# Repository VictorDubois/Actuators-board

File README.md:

Compact ESP32-based PCB, to control:
- 2 steppers
- 8 hobby servomotors (dedicated 6V DC-DC)
- AX12 Dynamixel numeric servomotors
- Addressable LEDs
- 2 vaccum sensors
- 4 generic GPIO connectors
- 3 generic I2C connectors
- 2 Krabi-Bus (12V/12V power/24V power/CAN)

[The code is available here](https://github.com/VictorDubois/ActuatorBoardCode)

[Click for online viewer

](https://kicanvas.org/?repo=https%3A%2F%2Fgithub.com%2FVictorDubois%2FActuators-board)

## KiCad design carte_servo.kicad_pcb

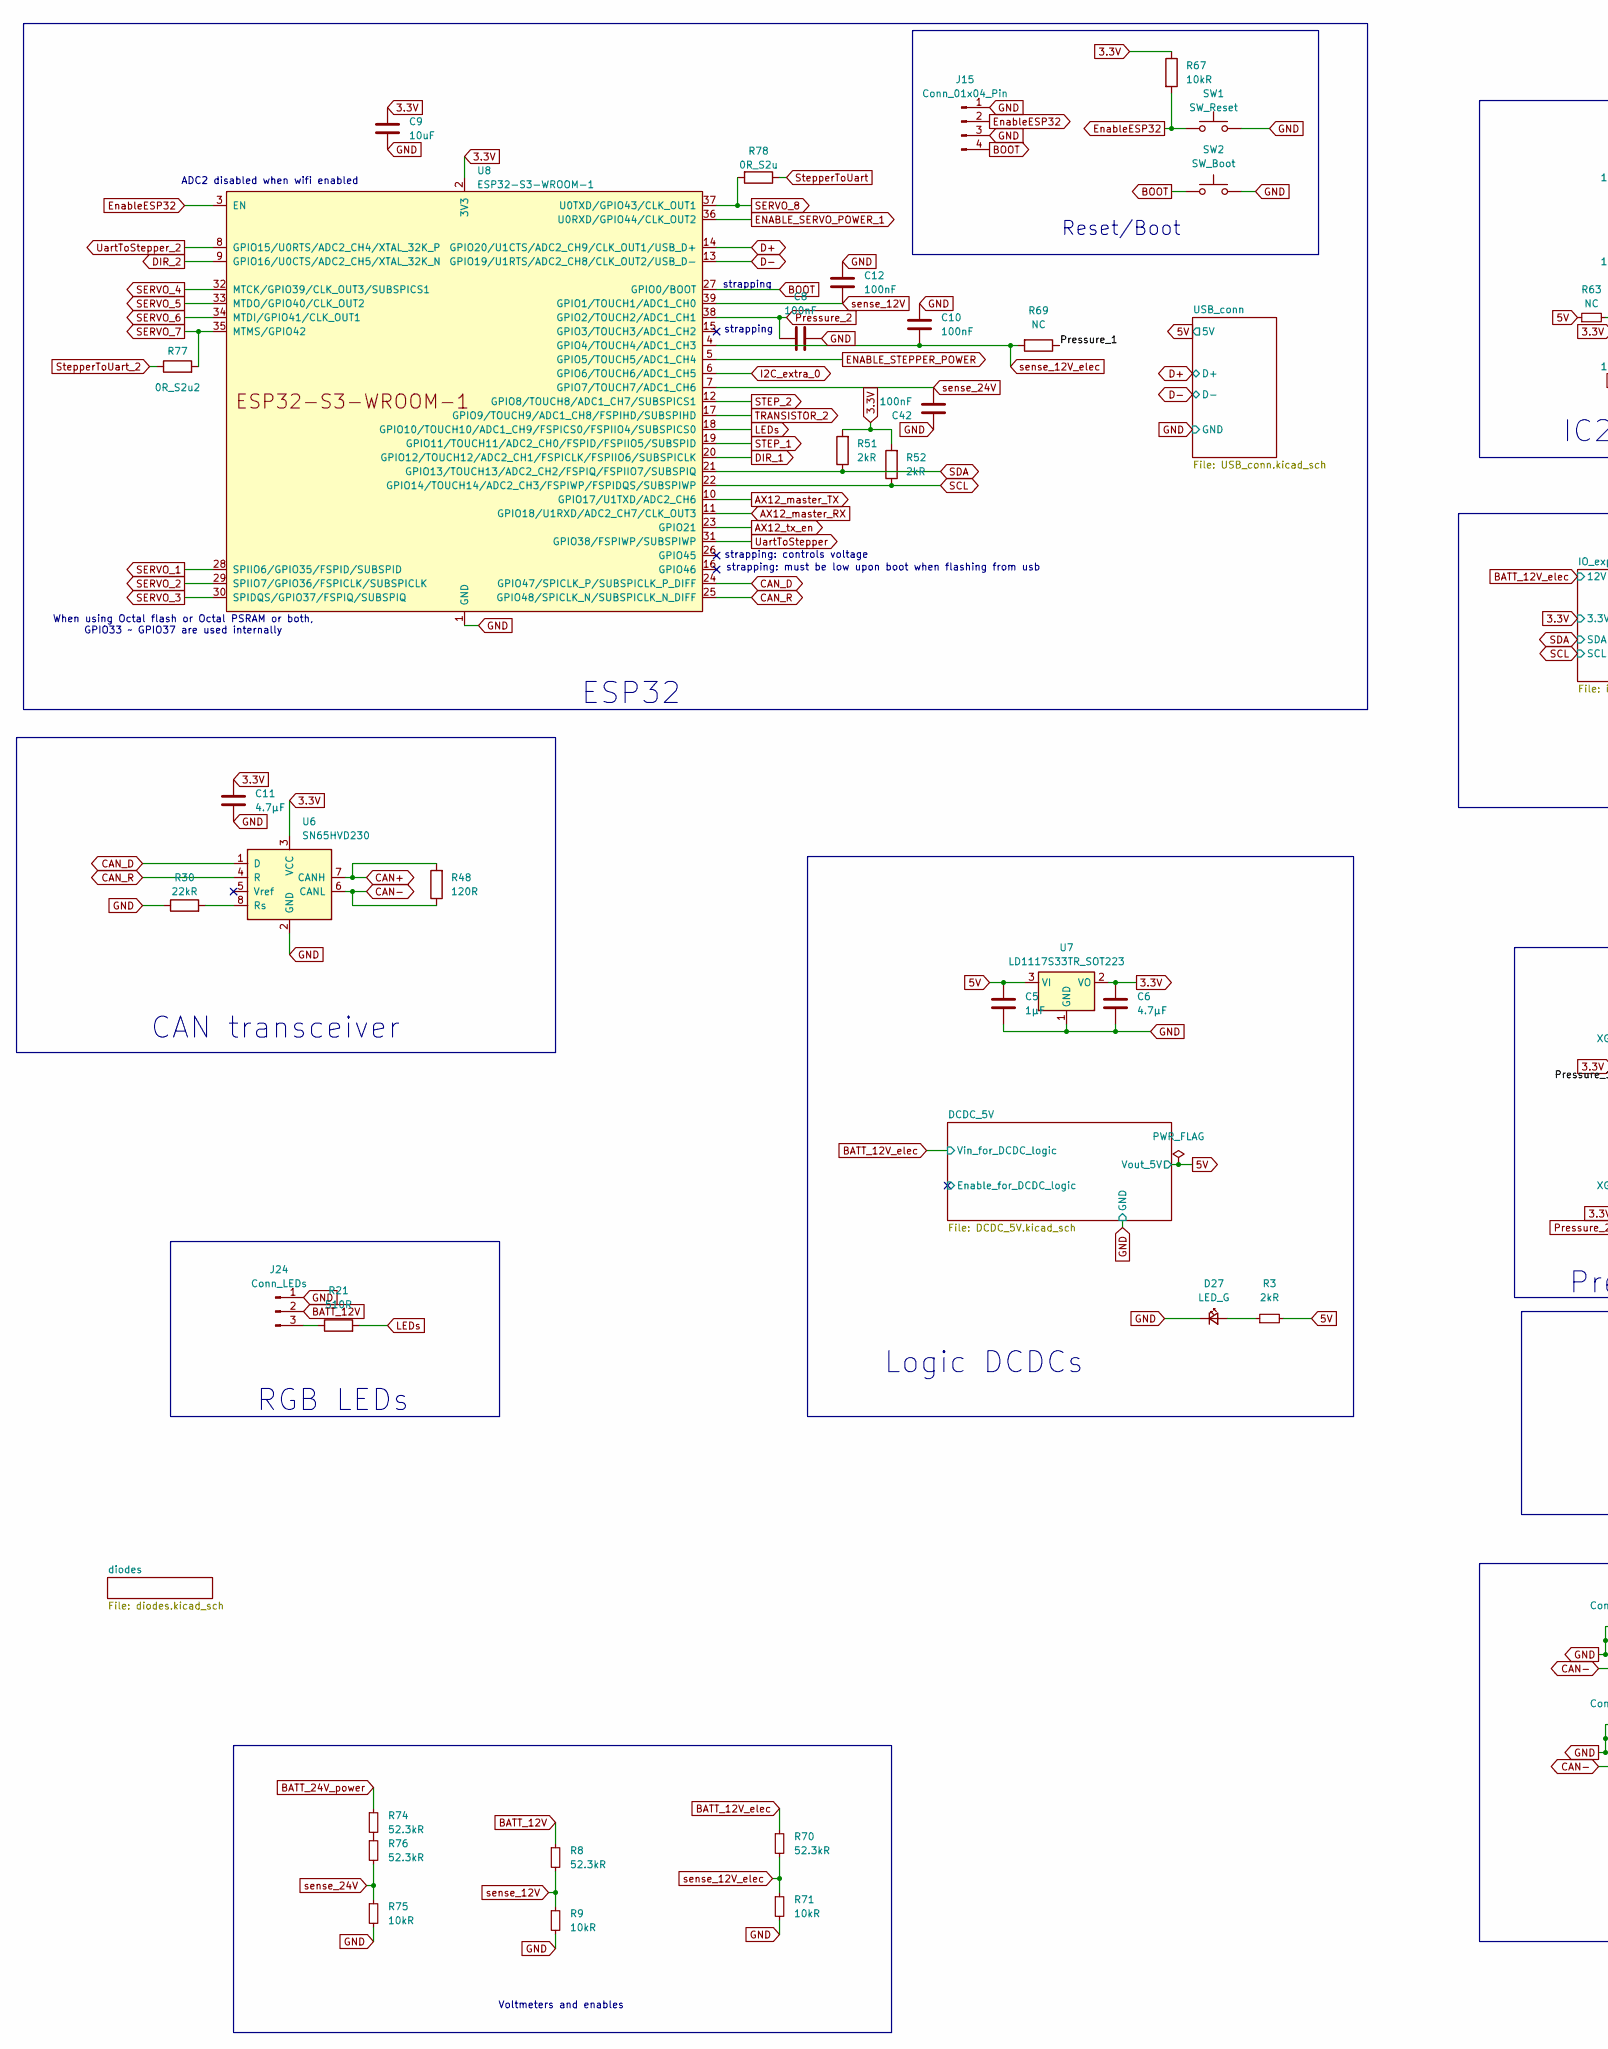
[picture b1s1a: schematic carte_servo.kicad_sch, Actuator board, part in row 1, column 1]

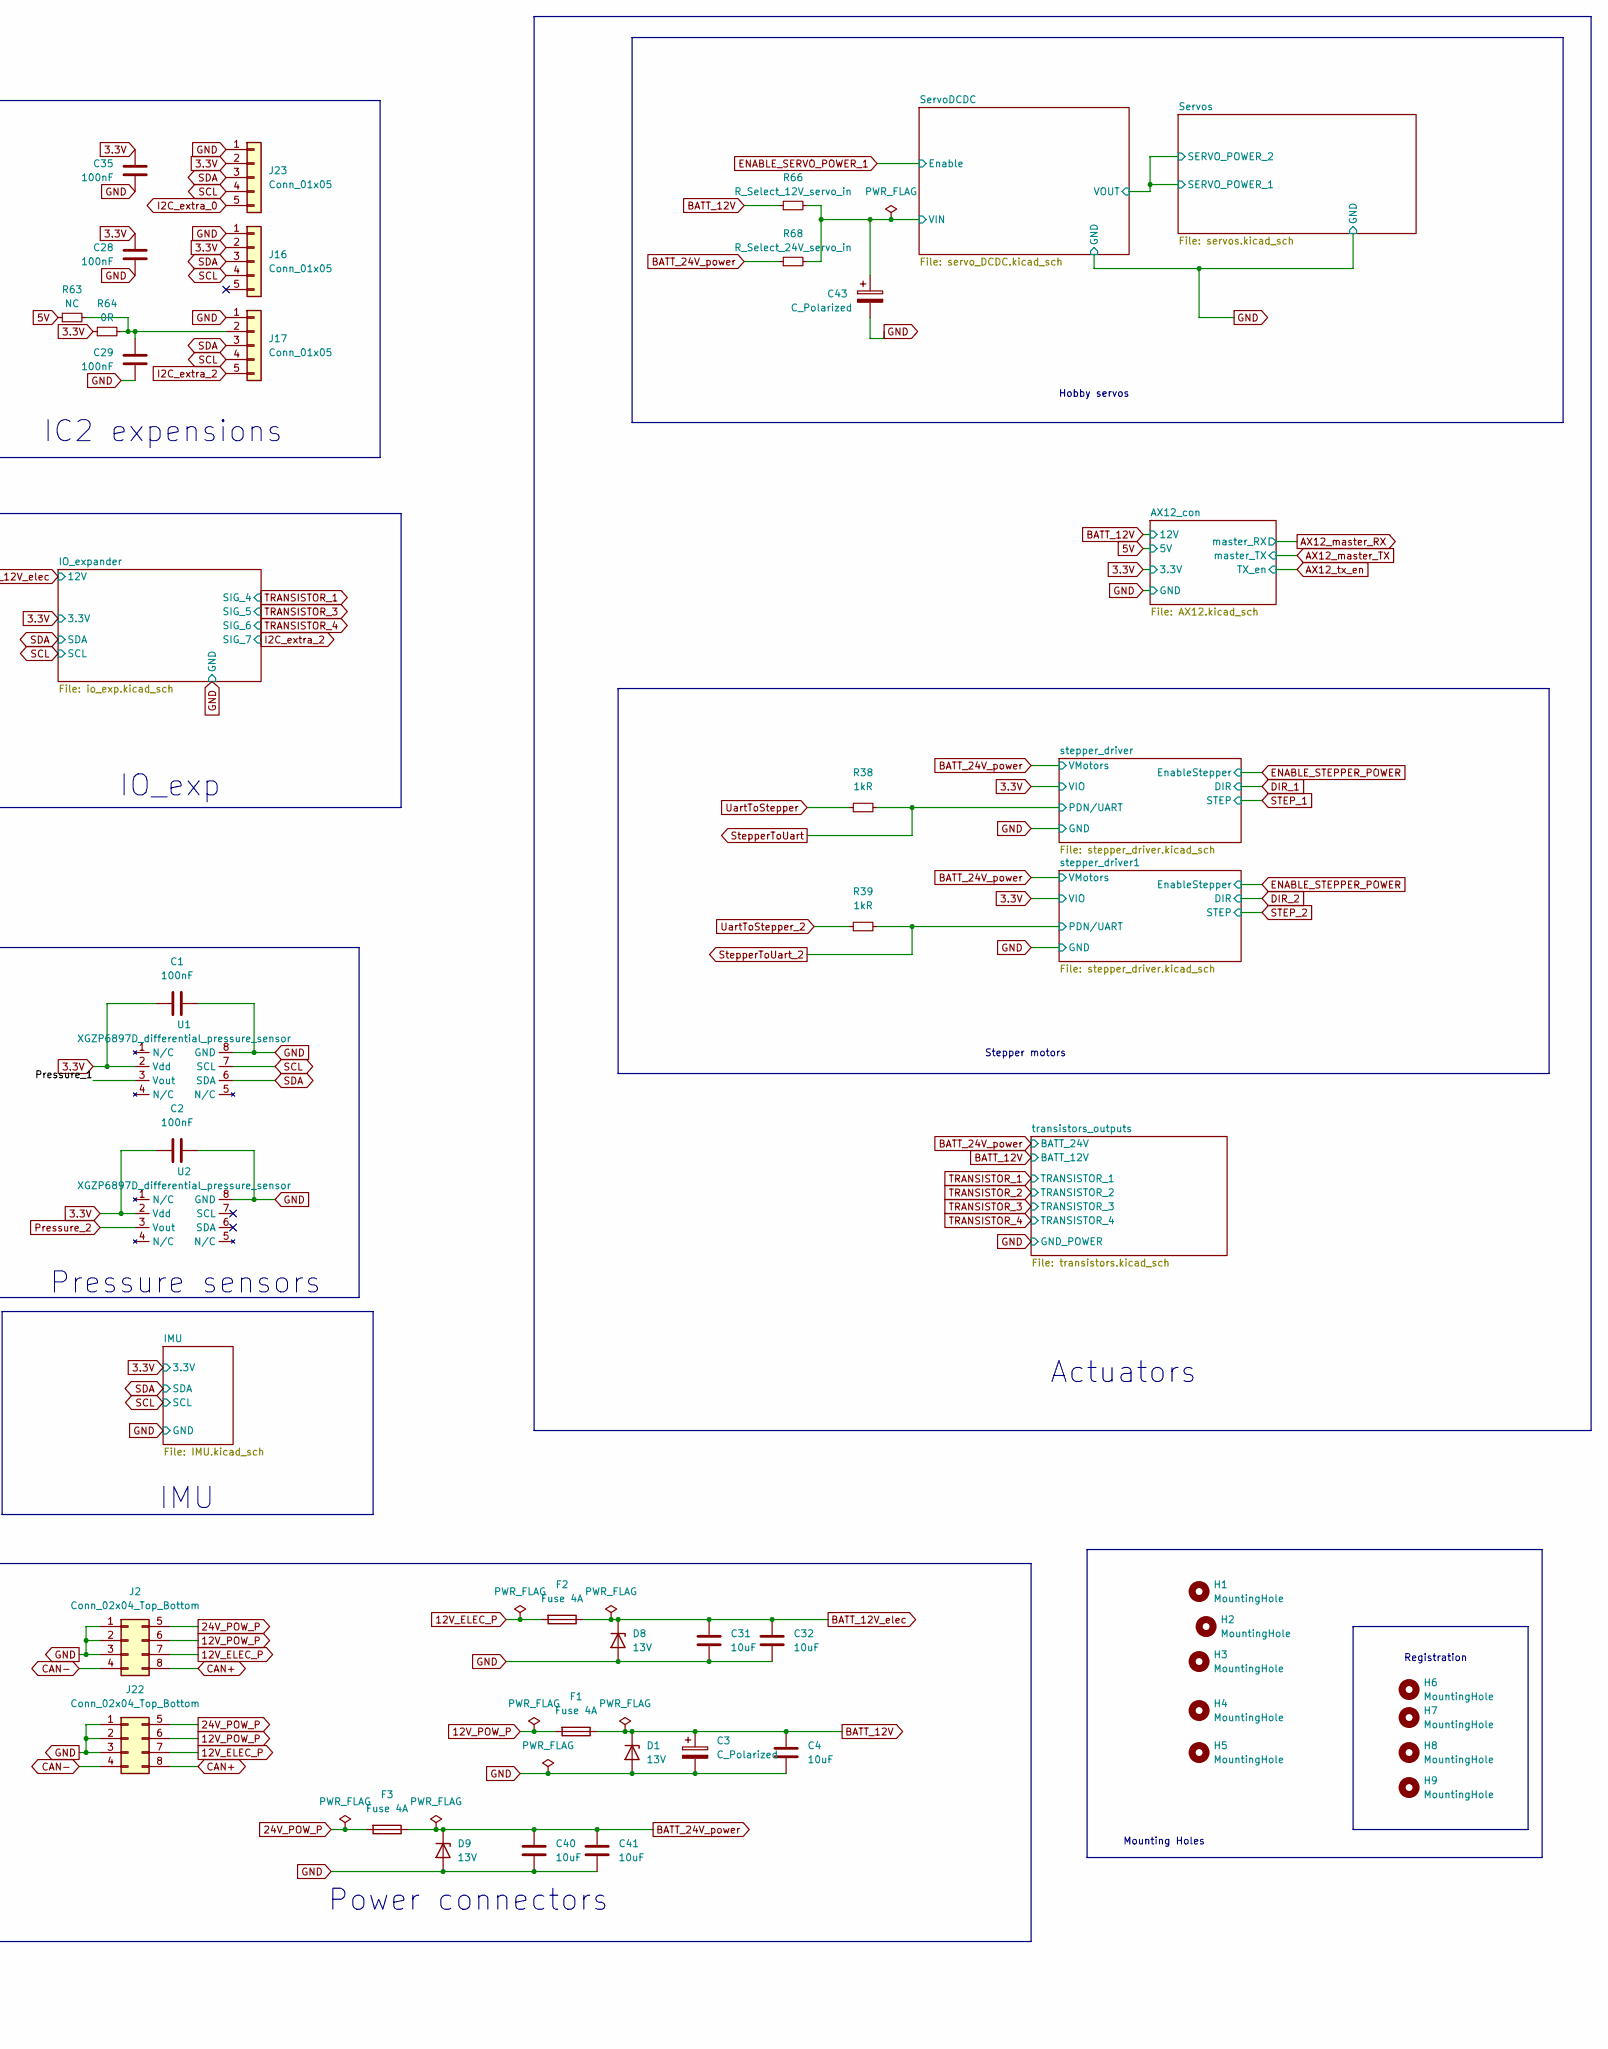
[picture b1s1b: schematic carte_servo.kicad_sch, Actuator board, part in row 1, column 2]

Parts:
C1, C2, C8, C10, C12, C28, C29, C35, C42: 100nF; C_0603_1608Metric; LCSC# C14663
C3: C_Polarized; CP_Radial_D10.0mm_P5.00mm; LCSC# C398835
C4, C9, C31, C32, C40, C41: 10uF; C_0805_2012Metric; LCSC# C440198
C5: 1µF; C_0603_1608Metric; LCSC# C15849
C6, C11: 4.7µF; C_0603_1608Metric; LCSC# C1705
C43: C_Polarized; CP_Elec_10x10.5; LCSC# C233118
D1, D8, D9: 13V; D_SOD-123; LCSC# C173428
D27: LED_G; LED_0805_2012Metric; LCSC# C965815
F1, F2, F3: Fuse 4A; Fuse_Littelfuse-NANO2-451_453; LCSC# C27515
H1, H2, H3, H4, H5: MountingHole; MountingHole_3.2mm_M3
H6, H7: MountingHole; MountingHole_3mm
H8, H9: MountingHole; MountingHole_5mm
J2, J22: Conn_02x04_Top_Bottom; Molex_Micro-Fit_3.0_43045-0812_2x04_P3.00mm_Vertical; LCSC# C277661
J15: Conn_01x04_Pin; JST_PH_B4B-PH-K_1x04_P2.00mm_Vertical; LCSC# C595709
J16, J17, J23: Conn_01x05; JST_XH_B5B-XH-A_1x05_P2.50mm_Vertical; LCSC# C495550
J24: Conn_LEDs; JST_XH_B3B-XH-A_1x03_P2.50mm_Vertical; LCSC# C144394
R3, R51, R52: 2kR; R_0603_1608Metric; LCSC# C2907137
R8, R70, R74, R76: 52.3kR; R_0603_1608Metric; LCSC# C23198
R9, R67, R71, R75: 10kR; R_0603_1608Metric; LCSC# C2930027
R21: 510R; R_0805_2012Metric; LCSC# C2907179
R30: 22kR; R_0603_1608Metric; LCSC# C2907128
R38, R39: 1kR; R_0603_1608Metric; LCSC# C2907113
R48: 120R; R_0603_1608Metric; LCSC# C2907128
R63, R69: NC; R_0603_1608Metric
R64: 0R; R_0603_1608Metric; LCSC# C21189
R66: R_Select_12V_servo_in; R_1206_3216Metric; LCSC# C2907406
R68: R_Select_24V_servo_in; R_1206_3216Metric; LCSC# C2907406
R77: 0R_S2u2; R_0603_1608Metric; LCSC# C2907128
R78: 0R_S2u; R_0603_1608Metric; LCSC# C2907128
SW1: SW_Reset; BZCN TSA007A1518B03; LCSC# C2888419
SW2: SW_Boot; BZCN TSA007A1518B03; LCSC# C2888419
U1, U2: XGZP6897D_differential_pressure_sensor; SOIC-8_7.5x5.85mm_P1.27mm
U6: SN65HVD230; SOIC-8_3.9x4.9mm_P1.27mm; LCSC# C12084
U7: LD1117S33TR_SOT223; SOT-223-3_TabPin2; LCSC# C20538890
U8: ESP32-S3-WROOM-1; ESP32-S3-WROOM-1U; LCSC# C2980297

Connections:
3.3V: C1.2, C2.2, C6.1, C9.1, C11.1, C28.1, C35.1, J16.2, J23.2, R51.2, R52.2, R64.1, R67.1, U1.2 (Vdd), U2.2 (Vdd), U6.3 (VCC), U7.2 (VO), U8.2 (3V3); also elsewhere on the board
5V: C5.1, R3.2, R63.1, U7.3 (VI); also elsewhere on the board
12V_ELEC_P: F2.2, J2.7, J22.7
12V_POW_P: F1.2, J2.6, J22.6
24V_POW_P: F3.2, J2.5, J22.5
/Pressure_1: R69.1, U1.3 (Vout)
/ServoDCDC/VIN: C43.1, R66.2, R68.2; also elsewhere on the board
AX12_master_RX: U8.11 (GPIO18/U1RXD/ADC2_CH7/CLK_OUT3); also elsewhere on the board
AX12_master_TX: U8.10 (GPIO17/U1TXD/ADC2_CH6); also elsewhere on the board
AX12_tx_en: U8.23 (GPIO21); also elsewhere on the board
BATT_12V: C3.1, C4.1, D1.1 (K), F1.1, J24.2, R8.1, R66.1; also elsewhere on the board
BATT_12V_elec: C31.1, C32.1, D8.1 (K), F2.1, R70.1; also elsewhere on the board
BATT_24V_power: C40.1, C41.1, D9.1 (K), F3.1, R68.1, R74.1; also elsewhere on the board
BOOT: J15.4, SW2.1, U8.27 (GPIO0/BOOT)
CAN+: J2.8, J22.8, R48.2, U6.7 (CANH)
CAN-: J2.4, J22.4, R48.1, U6.6 (CANL)
CAN_D: U6.1 (D), U8.24 (GPIO47/SPICLK_P/SUBSPICLK_P_DIFF)
CAN_R: U6.4 (R), U8.25 (GPIO48/SPICLK_N/SUBSPICLK_N_DIFF)
D+: U8.14 (GPIO20/U1CTS/ADC2_CH9/CLK_OUT1/USB_D+); also elsewhere on the board
D-: U8.13 (GPIO19/U1RTS/ADC2_CH8/CLK_OUT2/USB_D-); also elsewhere on the board
DIR_1: U8.20 (GPIO12/TOUCH12/ADC2_CH1/FSPICLK/FSPIIO6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); also elsewhere on the board
DIR_2: U8.9 (GPIO16/U0CTS/ADC2_CH5/XTAL_32K_N); also elsewhere on the board
ENABLE_SERVO_POWER_1: U8.36 (U0RXD/GPIO44/CLK_OUT2); also elsewhere on the board
ENABLE_STEPPER_POWER: U8.5 (GPIO5/TOUCH5/ADC1_CH4); also elsewhere on the board
EnableESP32: J15.2, R67.2, SW1.1, U8.3 (EN)
GND: C1.1, C2.1, C3.2, C4.2, C5.2, C6.2, C8.2, C9.2, C10.1, C11.2, C12.1, C28.2, C29.2, C31.2, C32.2, C35.2, C40.2, C41.2, C42.1, C43.2, D1.2 (A), D8.2 (A), D9.2 (A), D27.1 (K), J2.1, J2.2, J2.3, J15.1, J15.3, J16.1, J17.1, J22.1, J22.2, J22.3, J23.1, J24.1, R9.2, R30.1, R71.2, R75.2, SW1.2, SW2.2, U1.8 (GND), U2.8 (GND), U6.2 (GND), U7.1 (GND), U8.1 (GND), U8.40 (GND), U8.41 (GND); also elsewhere on the board
I2C_extra_0: J23.5, U8.6 (GPIO6/TOUCH6/ADC1_CH5)
I2C_extra_2: J17.5; also elsewhere on the board
LEDs: R21.2, U8.18 (GPIO10/TOUCH10/ADC1_CH9/FSPICS0/FSPIIO4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); also elsewhere on the board
unnamed: D27.2 (A), R3.1
unnamed: C29.1, J17.2, R63.2, R64.2
unnamed: J24.3, R21.1
unnamed: R74.2, R76.1
unnamed: R30.2, U6.8 (Rs)
Pressure_2: C8.1, U2.3 (Vout), U8.38 (GPIO2/TOUCH2/ADC1_CH1)
SCL: J16.4, J17.4, J23.4, R52.1, U1.7 (SCL), U8.22 (GPIO14/TOUCH14/ADC2_CH3/FSPIWP/FSPIDQS/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); also elsewhere on the board
SDA: J16.3, J17.3, J23.3, R51.1, U1.6 (SDA), U8.21 (GPIO13/TOUCH13/ADC2_CH2/FSPIQ/FSPIIO7/S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); also elsewhere on the board
SERVO_1: U8.28 (SPIIO6/GPIO35/FSPID/SUBSPID); also elsewhere on the board
SERVO_2: U8.29 (SPIIO7/GPIO36/FSPICLK/SUBSPICLK); also elsewhere on the board
SERVO_3: U8.30 (SPIDQS/GPIO37/FSPIQ/SUBSPIQ); also elsewhere on the board
SERVO_4: U8.32 (MTCK/GPIO39/CLK_OUT3/SUBSPICS1); also elsewhere on the board
SERVO_5: U8.33 (MTDO/GPIO40/CLK_OUT2); also elsewhere on the board
SERVO_6: U8.34 (MTDI/GPIO41/CLK_OUT1); also elsewhere on the board
SERVO_7: R77.2, U8.35 (MTMS/GPIO42); also elsewhere on the board
SERVO_8: R78.2, U8.37 (U0TXD/GPIO43/CLK_OUT1); also elsewhere on the board
STEP_1: U8.19 (GPIO11/TOUCH11/ADC2_CH0/FSPID/FSPIIO5/S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); also elsewhere on the board
STEP_2: U8.12 (GPIO8/TOUCH8/ADC1_CH7/SUBSPICS1); also elsewhere on the board
StepperToUart: R38.2, R78.1; also elsewhere on the board
StepperToUart_2: R39.2, R77.1; also elsewhere on the board
TRANSISTOR_2: U8.17 (GPIO9/TOUCH9/ADC1_CH8/FSPIHD/SUBSPIHD); also elsewhere on the board
UartToStepper: R38.1, U8.31 (GPIO38/FSPIWP/SUBSPIWP)
UartToStepper_2: R39.1, U8.8 (GPIO15/U0RTS/ADC2_CH4/XTAL_32K_P)
sense_12V: C12.2, R8.2, R9.1, U8.39 (GPIO1/TOUCH1/ADC1_CH0)
sense_12V_elec: C10.2, R69.2, R70.2, R71.1, U8.4 (GPIO4/TOUCH4/ADC1_CH3)
sense_24V: C42.2, R75.1, R76.2, U8.7 (GPIO7/TOUCH7/ADC1_CH6)

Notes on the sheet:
IMU
IO_exp
ADC2 disabled when wifi enabled
Hobby servos
strapping: must be low upon boot when flashing from usb
Voltmeters and enables
When using Octal flash or Octal PSRAM or both, GPIO33 ~ GPIO37 are used internally
Actuators
strapping
Registration
Power connectors
Stepper motors
strapping: controls voltage
IC2 expensions
ESP32
CAN transceiver
Logic DCDCs
RGB LEDs
Pressure sensors
Reset/Boot
Mounting Holes

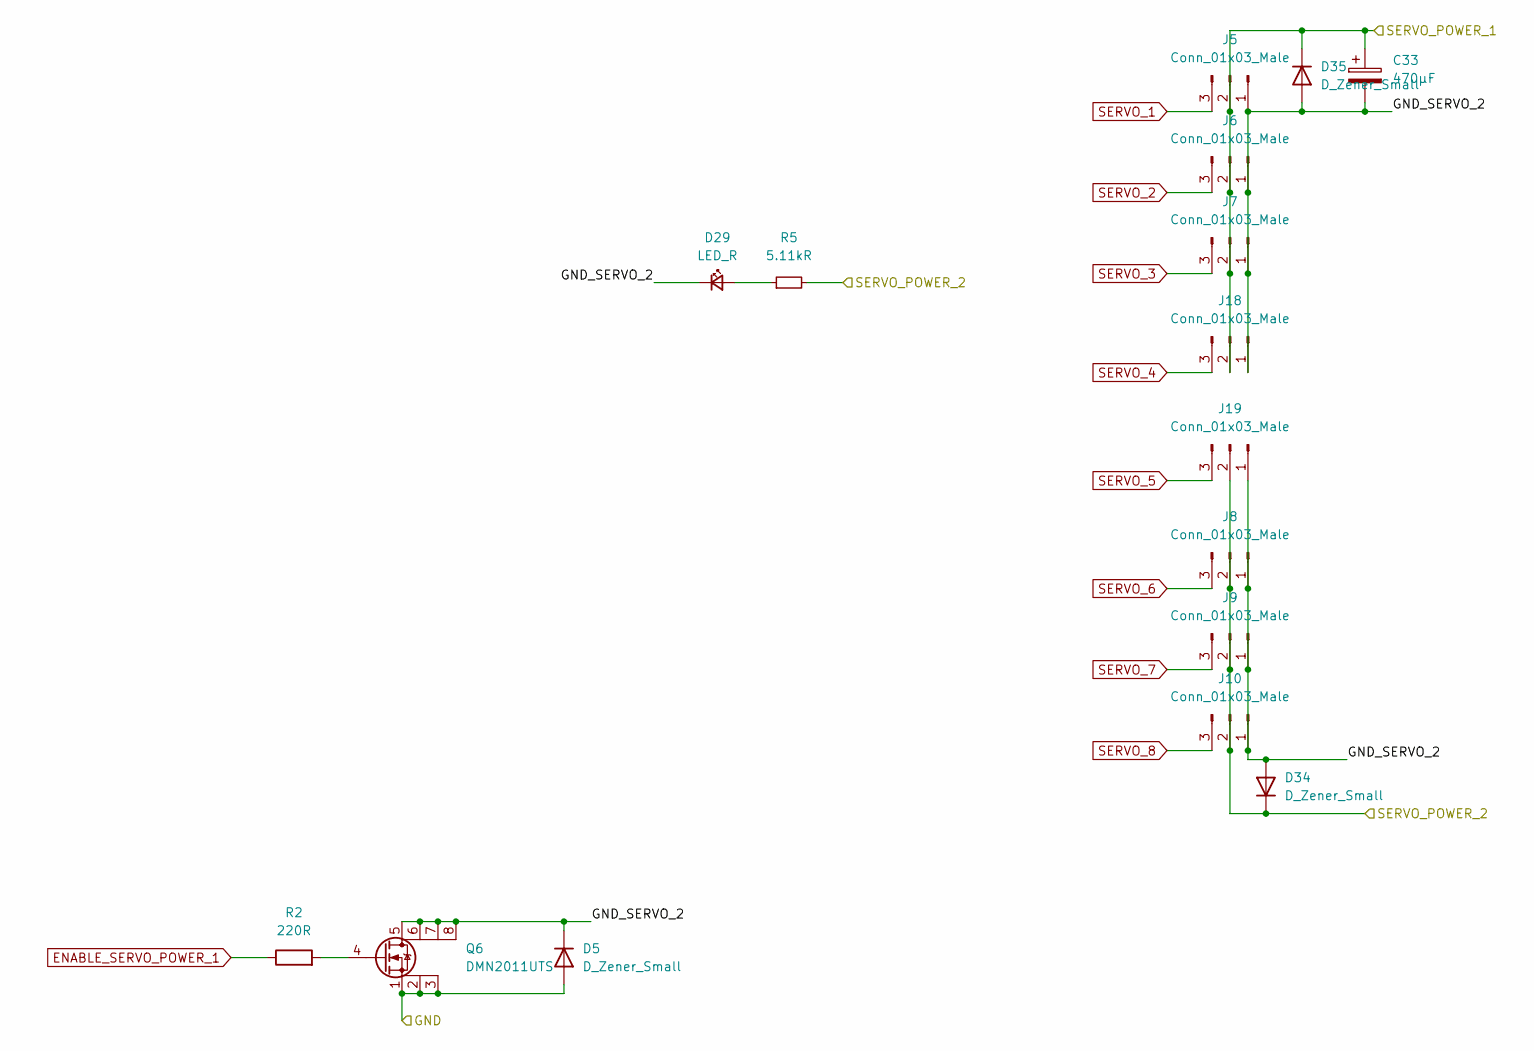
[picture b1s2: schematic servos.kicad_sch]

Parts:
C33: 470µF; CP_Radial_D7.5mm_P2.50mm; LCSC# C106619
D5, D34, D35: D_Zener_Small; D_SOD-123; LCSC# C908230
D29: LED_R; LED_0805_2012Metric; LCSC# C965812
J5, J6, J7, J8, J9, J10, J18, J19: Conn_01x03_Male; PinHeader_1x03_P2.54mm_Vertical; LCSC# C2937625
Q6: DMN2011UTS; TSSOP-8_4.4x3mm_P0.65mm; LCSC# C5245271
R2: 220R; R_0603_1608Metric; LCSC# C2907127
R5: 5.11kR; R_0603_1608Metric; LCSC# C2933233

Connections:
/ServoDCDC/VOUT: C33.1, D34.1 (K), D35.1 (K), J5.2, J6.2, J7.2, J8.2, J9.2, J10.2, J18.2, J19.2, R5.2; also elsewhere on the board
/Servos/GND_SERVO_2: C33.2, D5.1 (K), D29.1 (K), D34.2 (A), D35.2 (A), J5.1, J6.1, J7.1, J8.1, J9.1, J10.1, J18.1, J19.1, Q6.5 (D), Q6.6 (D), Q6.7 (D), Q6.8 (D)
ENABLE_SERVO_POWER_1: R2.1; also elsewhere on the board
GND: D5.2 (A), Q6.1 (S), Q6.2 (S), Q6.3 (S); also elsewhere on the board
unnamed: D29.2 (A), R5.1
unnamed: Q6.4 (G), R2.2
SERVO_1: J5.3; also elsewhere on the board
SERVO_2: J6.3; also elsewhere on the board
SERVO_3: J7.3; also elsewhere on the board
SERVO_4: J18.3; also elsewhere on the board
SERVO_5: J19.3; also elsewhere on the board
SERVO_6: J8.3; also elsewhere on the board
SERVO_7: J9.3; also elsewhere on the board
SERVO_8: J10.3; also elsewhere on the board

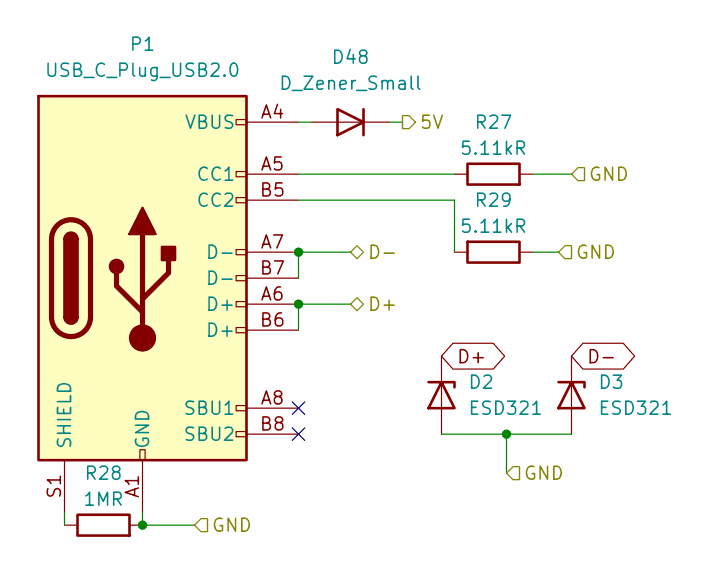
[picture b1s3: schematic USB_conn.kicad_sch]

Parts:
D2, D3: ESD321; D_SOD-523; LCSC# C3008120
D48: D_Zener_Small; D_SOD-123; LCSC# C908230
P1: USB_C_Plug_USB2.0; G-Switch GT-USB-7047A; LCSC# C963216
R27, R29: 5.11kR; R_0603_1608Metric; LCSC# C2933233
R28: 1MR; R_0603_1608Metric; LCSC# C22935

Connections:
5V: D48.1 (K); also elsewhere on the board
D+: D2.1 (K), P1.A6 (D+), P1.B6 (D+); also elsewhere on the board
D-: D3.1 (K), P1.A7 (D-), P1.B7 (D-); also elsewhere on the board
GND: D2.2 (A), D3.2 (A), P1.A1 (GND), P1.A12 (GND), P1.B1 (GND), P1.B12 (GND), R27.2, R28.2, R29.1; also elsewhere on the board
unnamed: D48.2 (A), P1.A4 (VBUS), P1.A9 (VBUS), P1.B4 (VBUS), P1.B9 (VBUS)
unnamed: P1.A5 (CC1), R27.1
unnamed: P1.B5 (CC2), R29.2
unnamed: P1.S1 (SHIELD), R28.1

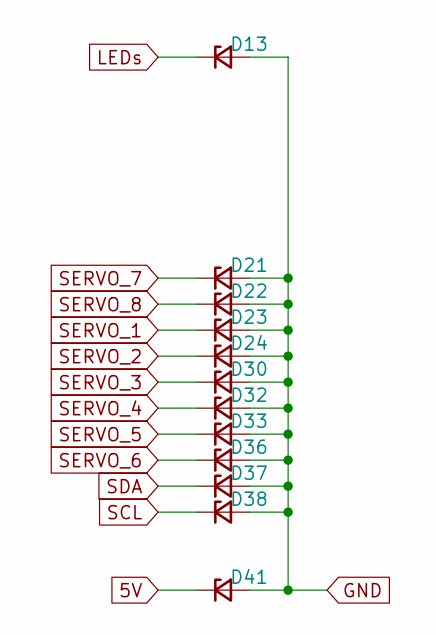
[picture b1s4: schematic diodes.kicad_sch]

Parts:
D13, D21, D22, D23, D24, D30, D32, D33, D36, D37, D38, D41: D_Zener_Small; D_SOD-123; LCSC# C908230

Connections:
5V: D41.1 (K); also elsewhere on the board
GND: D13.2 (A), D21.2 (A), D22.2 (A), D23.2 (A), D24.2 (A), D30.2 (A), D32.2 (A), D33.2 (A), D36.2 (A), D37.2 (A), D38.2 (A), D41.2 (A); also elsewhere on the board
LEDs: D13.1 (K); also elsewhere on the board
SCL: D38.1 (K); also elsewhere on the board
SDA: D37.1 (K); also elsewhere on the board
SERVO_1: D23.1 (K); also elsewhere on the board
SERVO_2: D24.1 (K); also elsewhere on the board
SERVO_3: D30.1 (K); also elsewhere on the board
SERVO_4: D32.1 (K); also elsewhere on the board
SERVO_5: D33.1 (K); also elsewhere on the board
SERVO_6: D36.1 (K); also elsewhere on the board
SERVO_7: D21.1 (K); also elsewhere on the board
SERVO_8: D22.1 (K); also elsewhere on the board

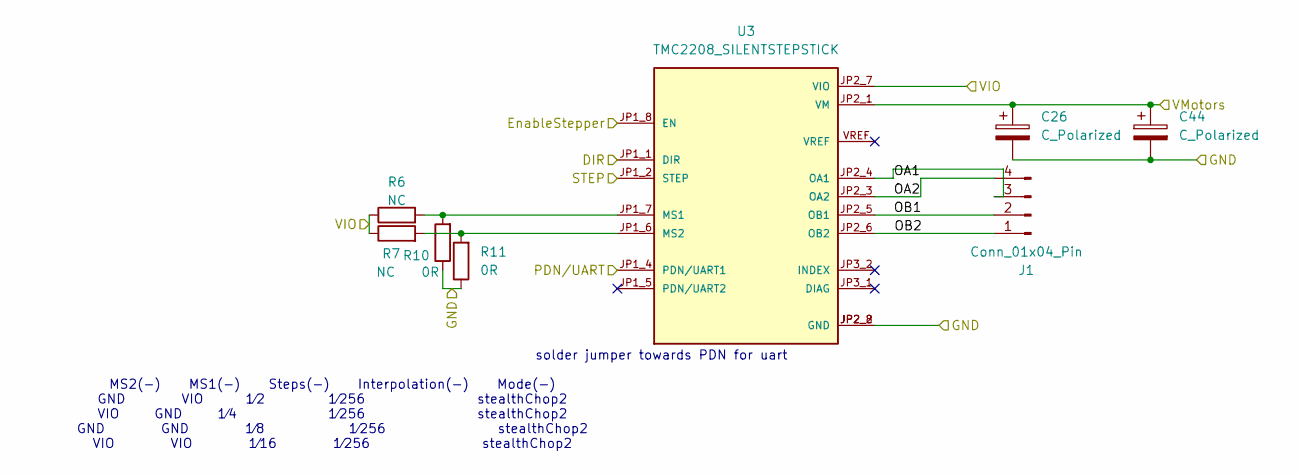
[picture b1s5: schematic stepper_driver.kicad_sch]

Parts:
C26: C_Polarized; CP_Radial_D10.0mm_P5.00mm; LCSC# C398835
C44: C_Polarized; CP_Elec_10x10.5; LCSC# C398835
J1: Conn_01x04_Pin; JST_XH_B4B-XH-A_1x04_P2.50mm_Vertical; LCSC# C595709
R6, R7: NC; R_0603_1608Metric
R10, R11: 0R; R_0603_1608Metric; LCSC# C21189
U3: TMC2208_SILENTSTEPSTICK; MODULE_TMC2208_SILENTSTEPSTICK

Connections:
3.3V: R6.1, R7.1, U3.JP2_7 (VIO); also elsewhere on the board
/stepper_driver/OA1: J1.3, U3.JP2_4 (OA1)
/stepper_driver/OA2: J1.4, U3.JP2_3 (OA2)
/stepper_driver/OB1: J1.2, U3.JP2_5 (OB1)
/stepper_driver/OB2: J1.1, U3.JP2_6 (OB2)
BATT_24V_power: C26.1, C44.1, U3.JP2_1 (VM); also elsewhere on the board
DIR_1: U3.JP1_1 (DIR); also elsewhere on the board
ENABLE_STEPPER_POWER: U3.JP1_8 (EN); also elsewhere on the board
GND: C26.2, C44.2, R10.1, R11.1, U3.JP2_2 (GND), U3.JP2_8 (GND); also elsewhere on the board
unnamed: R6.2, R10.2, U3.JP1_7 (MS1)
unnamed: R7.2, R11.2, U3.JP1_6 (MS2)
STEP_1: U3.JP1_2 (STEP); also elsewhere on the board
StepperToUart: U3.JP1_4 (PDN/UART1); also elsewhere on the board

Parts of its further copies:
C27: C_Polarized; CP_Radial_D10.0mm_P5.00mm; LCSC# C398835
C45: C_Polarized; CP_Elec_10x10.5; LCSC# C398835
J3: Conn_01x04_Pin; JST_XH_B4B-XH-A_1x04_P2.50mm_Vertical; LCSC# C595709
R13, R14: NC; R_0603_1608Metric
R15, R16: 0R; R_0603_1608Metric; LCSC# C21189
U4: TMC2208_SILENTSTEPSTICK; MODULE_TMC2208_SILENTSTEPSTICK

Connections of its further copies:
3.3V: R13.1, R14.1, U4.JP2_7 (VIO); also elsewhere on the board
/stepper_driver1/OA1: J3.3, U4.JP2_4 (OA1)
/stepper_driver1/OA2: J3.4, U4.JP2_3 (OA2)
/stepper_driver1/OB1: J3.2, U4.JP2_5 (OB1)
/stepper_driver1/OB2: J3.1, U4.JP2_6 (OB2)
BATT_24V_power: C27.1, C45.1, U4.JP2_1 (VM); also elsewhere on the board
DIR_2: U4.JP1_1 (DIR); also elsewhere on the board
ENABLE_STEPPER_POWER: U4.JP1_8 (EN); also elsewhere on the board
GND: C27.2, C45.2, R15.1, R16.1, U4.JP2_2 (GND), U4.JP2_8 (GND); also elsewhere on the board
unnamed: R13.2, R15.2, U4.JP1_7 (MS1)
unnamed: R14.2, R16.2, U4.JP1_6 (MS2)
STEP_2: U4.JP1_2 (STEP); also elsewhere on the board
StepperToUart_2: U4.JP1_4 (PDN/UART1); also elsewhere on the board

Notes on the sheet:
solder jumper towards PDN for uart
MS2(-) MS1(-) Steps(-) Interpolation(-) Mode(-) GND VIO 1⁄2 1⁄256 stealthChop2 VIO GND 1⁄4 1⁄256 stealthChop2 GND GND 1⁄8 1⁄256 stealthChop2 VIO VIO 1⁄16 1⁄256 stealthChop2

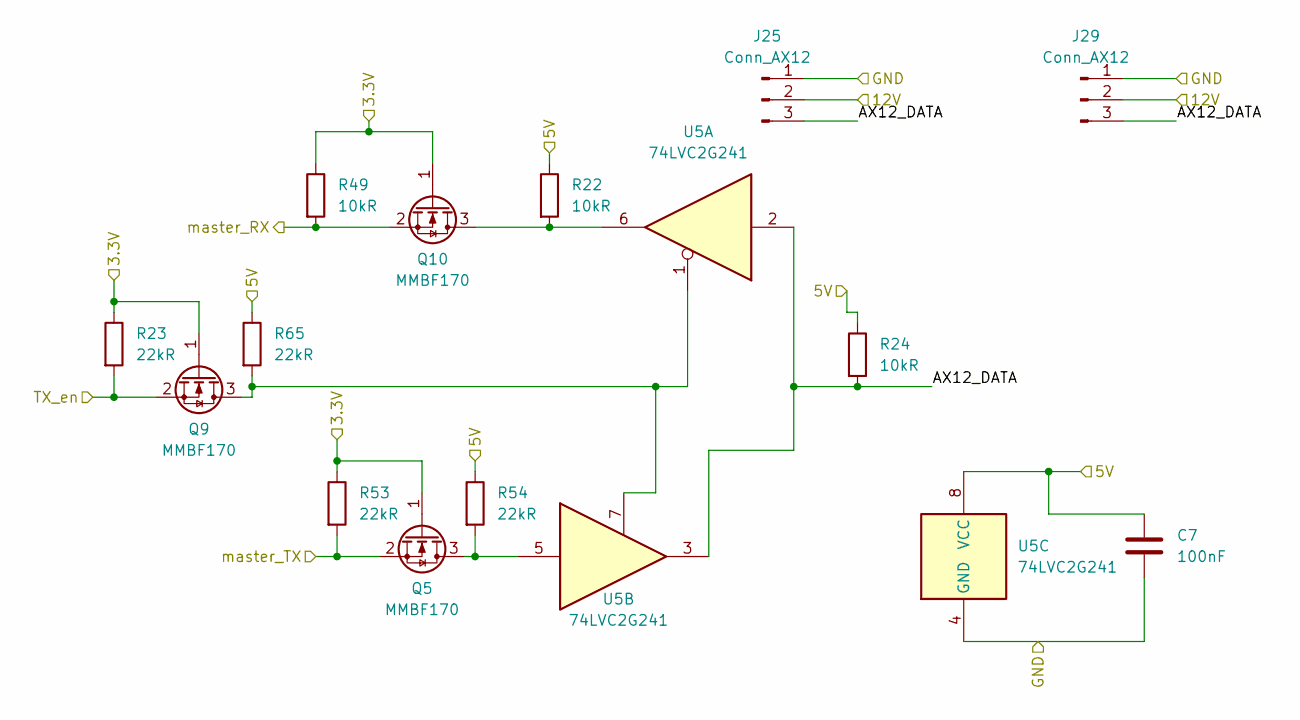
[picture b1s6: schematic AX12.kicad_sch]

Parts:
C7: 100nF; C_0603_1608Metric; LCSC# C14663
J25, J29: Conn_AX12; JST_XH_B3B-XH-A_1x03_P2.50mm_Vertical; LCSC# C144394
Q5, Q9, Q10: MMBF170; SOT-23; LCSC# C28871
R22, R24, R49: 10kR; R_0603_1608Metric; LCSC# C2930027
R23, R53, R54, R65: 22kR; R_0603_1608Metric; LCSC# C2907128
U5: 74LVC2G241; VSSOP-8_2.4x2.1mm_P0.5mm; LCSC# C10430

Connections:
3.3V: Q5.1 (G), Q9.1 (G), Q10.1 (G), R23.1, R49.1, R53.1; also elsewhere on the board
5V: C7.1, R22.1, R24.1, R54.1, R65.1, U5.8 (VCC); also elsewhere on the board
/AX12_con/AX12_DATA: J25.3, J29.3, R24.2, U5.2, U5.3
AX12_master_RX: Q10.2 (S), R49.2; also elsewhere on the board
AX12_master_TX: Q5.2 (S), R53.2; also elsewhere on the board
AX12_tx_en: Q9.2 (S), R23.2; also elsewhere on the board
BATT_12V: J25.2, J29.2; also elsewhere on the board
GND: C7.2, J25.1, J29.1, U5.4 (GND); also elsewhere on the board
unnamed: Q5.3 (D), R54.2, U5.5
unnamed: Q9.3 (D), R65.2, U5.1, U5.7
unnamed: Q10.3 (D), R22.2, U5.6

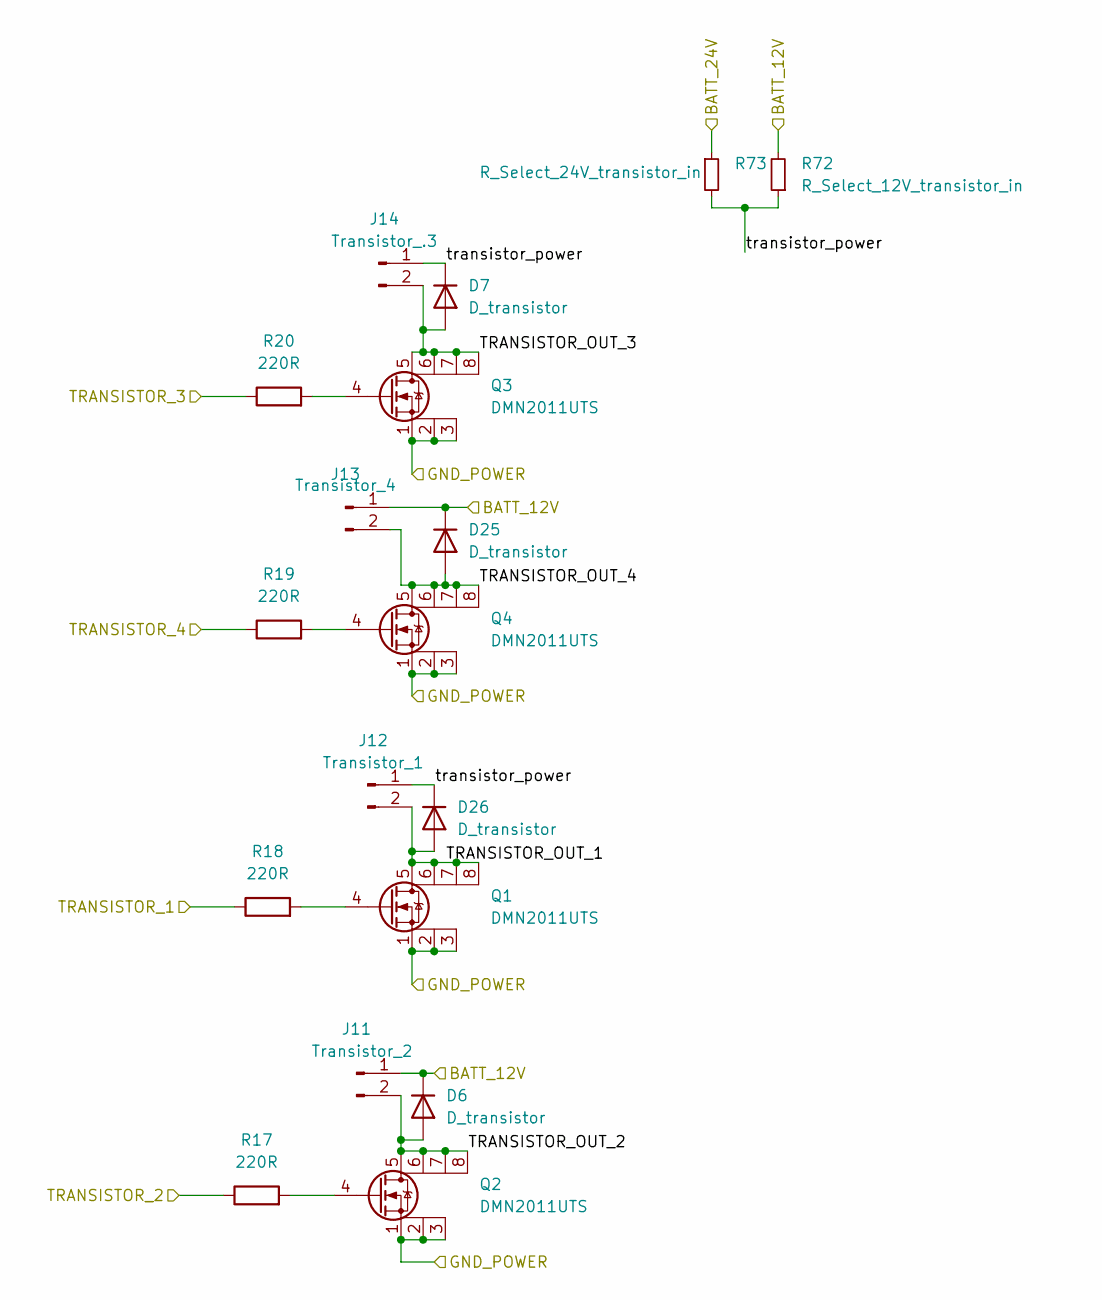
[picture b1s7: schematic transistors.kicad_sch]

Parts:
D6, D7, D25, D26: D_transistor; D_SOD-123; LCSC# C908230
J11: Transistor_2; JST_XH_B2B-XH-A_1x02_P2.50mm_Vertical; LCSC# C158012
J12: Transistor_1; JST_XH_B2B-XH-A_1x02_P2.50mm_Vertical; LCSC# C158012
J13: Transistor_4; JST_XH_B2B-XH-A_1x02_P2.50mm_Vertical; LCSC# C158012
J14: Transistor_.3; JST_XH_B2B-XH-A_1x02_P2.50mm_Vertical; LCSC# C158012
Q1, Q2, Q3, Q4: DMN2011UTS; TSSOP-8_4.4x3mm_P0.65mm; LCSC# C5245271
R17, R18, R19, R20: 220R; R_0603_1608Metric; LCSC# C2907127
R72: R_Select_12V_transistor_in; R_1206_3216Metric; LCSC# C2907406
R73: R_Select_24V_transistor_in; R_1206_3216Metric; LCSC# C2907406

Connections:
/transistors_outputs/TRANSISTOR_OUT_1: D26.2 (A), J12.2, Q1.5 (D), Q1.6 (D), Q1.7 (D), Q1.8 (D)
/transistors_outputs/TRANSISTOR_OUT_2: D6.2 (A), J11.2, Q2.5 (D), Q2.6 (D), Q2.7 (D), Q2.8 (D)
/transistors_outputs/TRANSISTOR_OUT_3: D7.2 (A), J14.2, Q3.5 (D), Q3.6 (D), Q3.7 (D), Q3.8 (D)
/transistors_outputs/TRANSISTOR_OUT_4: D25.2 (A), J13.2, Q4.5 (D), Q4.6 (D), Q4.7 (D), Q4.8 (D)
/transistors_outputs/transistor_power: D7.1 (K), D26.1 (K), J12.1, J14.1, R72.1, R73.2
BATT_12V: D6.1 (K), D25.1 (K), J11.1, J13.1, R72.2; also elsewhere on the board
BATT_24V_power: R73.1; also elsewhere on the board
GND: Q1.1 (S), Q1.2 (S), Q1.3 (S), Q2.1 (S), Q2.2 (S), Q2.3 (S), Q3.1 (S), Q3.2 (S), Q3.3 (S), Q4.1 (S), Q4.2 (S), Q4.3 (S); also elsewhere on the board
unnamed: Q1.4 (G), R18.2
unnamed: Q2.4 (G), R17.2
unnamed: Q3.4 (G), R20.2
unnamed: Q4.4 (G), R19.2
TRANSISTOR_1: R18.1; also elsewhere on the board
TRANSISTOR_2: R17.1; also elsewhere on the board
TRANSISTOR_3: R20.1; also elsewhere on the board
TRANSISTOR_4: R19.1; also elsewhere on the board

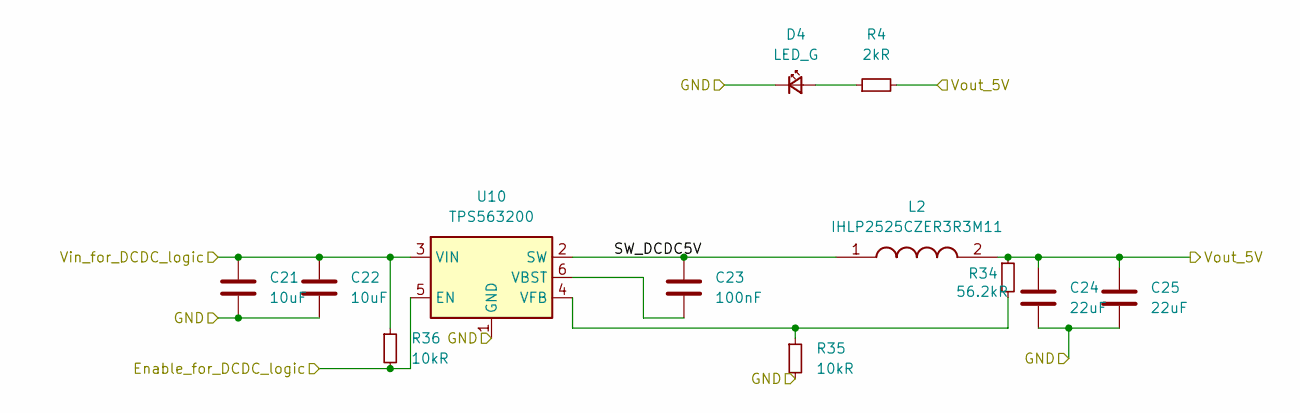
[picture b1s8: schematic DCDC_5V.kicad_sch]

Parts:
C21, C22: 10uF; C_0805_2012Metric; LCSC# C440198
C23: 100nF; C_0603_1608Metric; LCSC# C14663
C24, C25: 22uF; LED_0805_2012Metric; LCSC# C29277
D4: LED_G; LED_0805_2012Metric; LCSC# C965815
L2: IHLP2525CZER3R3M11; INDPM6965X300N; LCSC# C845025
R4: 2kR; R_0603_1608Metric; LCSC# C2907137
R34: 56.2kR; C_0603_1608Metric; LCSC# C2930117
R35, R36: 10kR; R_0603_1608Metric; LCSC# C2930027
U10: TPS563200; SOT-23-6; LCSC# C97253

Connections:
5V: C24.1, C25.1, L2.2, R4.2, R34.1; also elsewhere on the board
/DCDC_5V/Enable_for_DCDC_logic: R36.2, U10.5 (EN)
/DCDC_5V/SW_DCDC5V: C23.1, L2.1, U10.2 (SW)
BATT_12V_elec: C21.1, C22.1, R36.1, U10.3 (VIN); also elsewhere on the board
GND: C21.2, C22.2, C24.2, C25.2, D4.1 (K), R35.2, U10.1 (GND); also elsewhere on the board
unnamed: D4.2 (A), R4.1
unnamed: C23.2, U10.6 (VBST)
unnamed: R34.2, R35.1, U10.4 (VFB)

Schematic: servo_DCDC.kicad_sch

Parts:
C13: 2.2uF; C_0805_2012Metric; LCSC# C19110
C14: 470nF; C_0603_1608Metric; LCSC# C2905413
C15: 68pF; C_0603_1608Metric; LCSC# C62782
C16, C17, C30: 47uF; C_1210_3225Metric; LCSC# C5440143
C18: 10nF (12V) - 15nF (24V); C_0603_1608Metric; LCSC# C296713
C19, C20: 10uF; C_0805_2012Metric; LCSC# C440198
L1: XAL6030-182MEB; IND_XAL6030-122MEC; PARTREV 11/02/18; LCSC# C19191693
Q7: CSD17307Q5A; TDSON-8-1; LCSC# C78118
Q8: CSD17579Q5A; TDSON-8-1; LCSC# C2760461
R1: 1.74kR; C_0603_1608Metric; LCSC# C2930053
R31: 52.3kR (12V) - 42.2kR (24V); R_0603_1608Metric; LCSC# C23167
R32: 88.7kR; C_0603_1608Metric; LCSC# C2999456
R33: 9.76kR; C_0603_1608Metric; LCSC# C2933269
U9: LM3150MH; Texas_HTSSOP-14-1EP_4.4x5mm_P0.65mm_EP3.4x5mm_Mask3.155x3.2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; LCSC# C1519420

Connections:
/ServoDCDC/SW: C14.1, L1.1, Q7.1 (S), Q7.2 (S), Q7.3 (S), Q8.5 (D), R1.2, U9.10 (SW)
/ServoDCDC/VIN: C19.2, C20.2, Q7.5 (D), R31.1, U9.2 (VIN); also elsewhere on the board
/ServoDCDC/VOUT: C15.2, C16.1, C17.1, C30.1, L1.2, R32.2; also elsewhere on the board
ENABLE_SERVO_POWER_1: U9.3 (EN); also elsewhere on the board
GND: C13.1, C16.2, C17.2, C18.1, C19.1, C20.1, C30.2, Q8.1 (S), Q8.2 (S), Q8.3 (S), R33.1, U9.5 (SGND), U9.9 (SGND), U9.14 (PGND), U9.15 (SGND); also elsewhere on the board
unnamed: Q7.4 (G), U9.11 (HG)
unnamed: Q8.4 (G), U9.13 (LG)
unnamed: C14.2, U9.12 (BST)
unnamed: C15.1, R32.1, R33.2, U9.4 (FB)
unnamed: R1.1, U9.8 (ILIM)
unnamed: R31.2, U9.7 (RON)
unnamed: C18.2, U9.6 (SS)
unnamed: C13.2, U9.1 (VCC)

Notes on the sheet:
24V input: L2 XAL6030-182MEB C19191693 (même empreinte) haut CSD18504Q5A C78118 (même empreinte) bas CSD18563Q5A C2760461 (même empreinte)
12V input: L2 XAL6030-122MEC C19191689 (même empreinte) haut CSD17307Q5A C22367097 (même empreinte) bas CSD17579Q5A CSD17579Q5A (même empreinte)
